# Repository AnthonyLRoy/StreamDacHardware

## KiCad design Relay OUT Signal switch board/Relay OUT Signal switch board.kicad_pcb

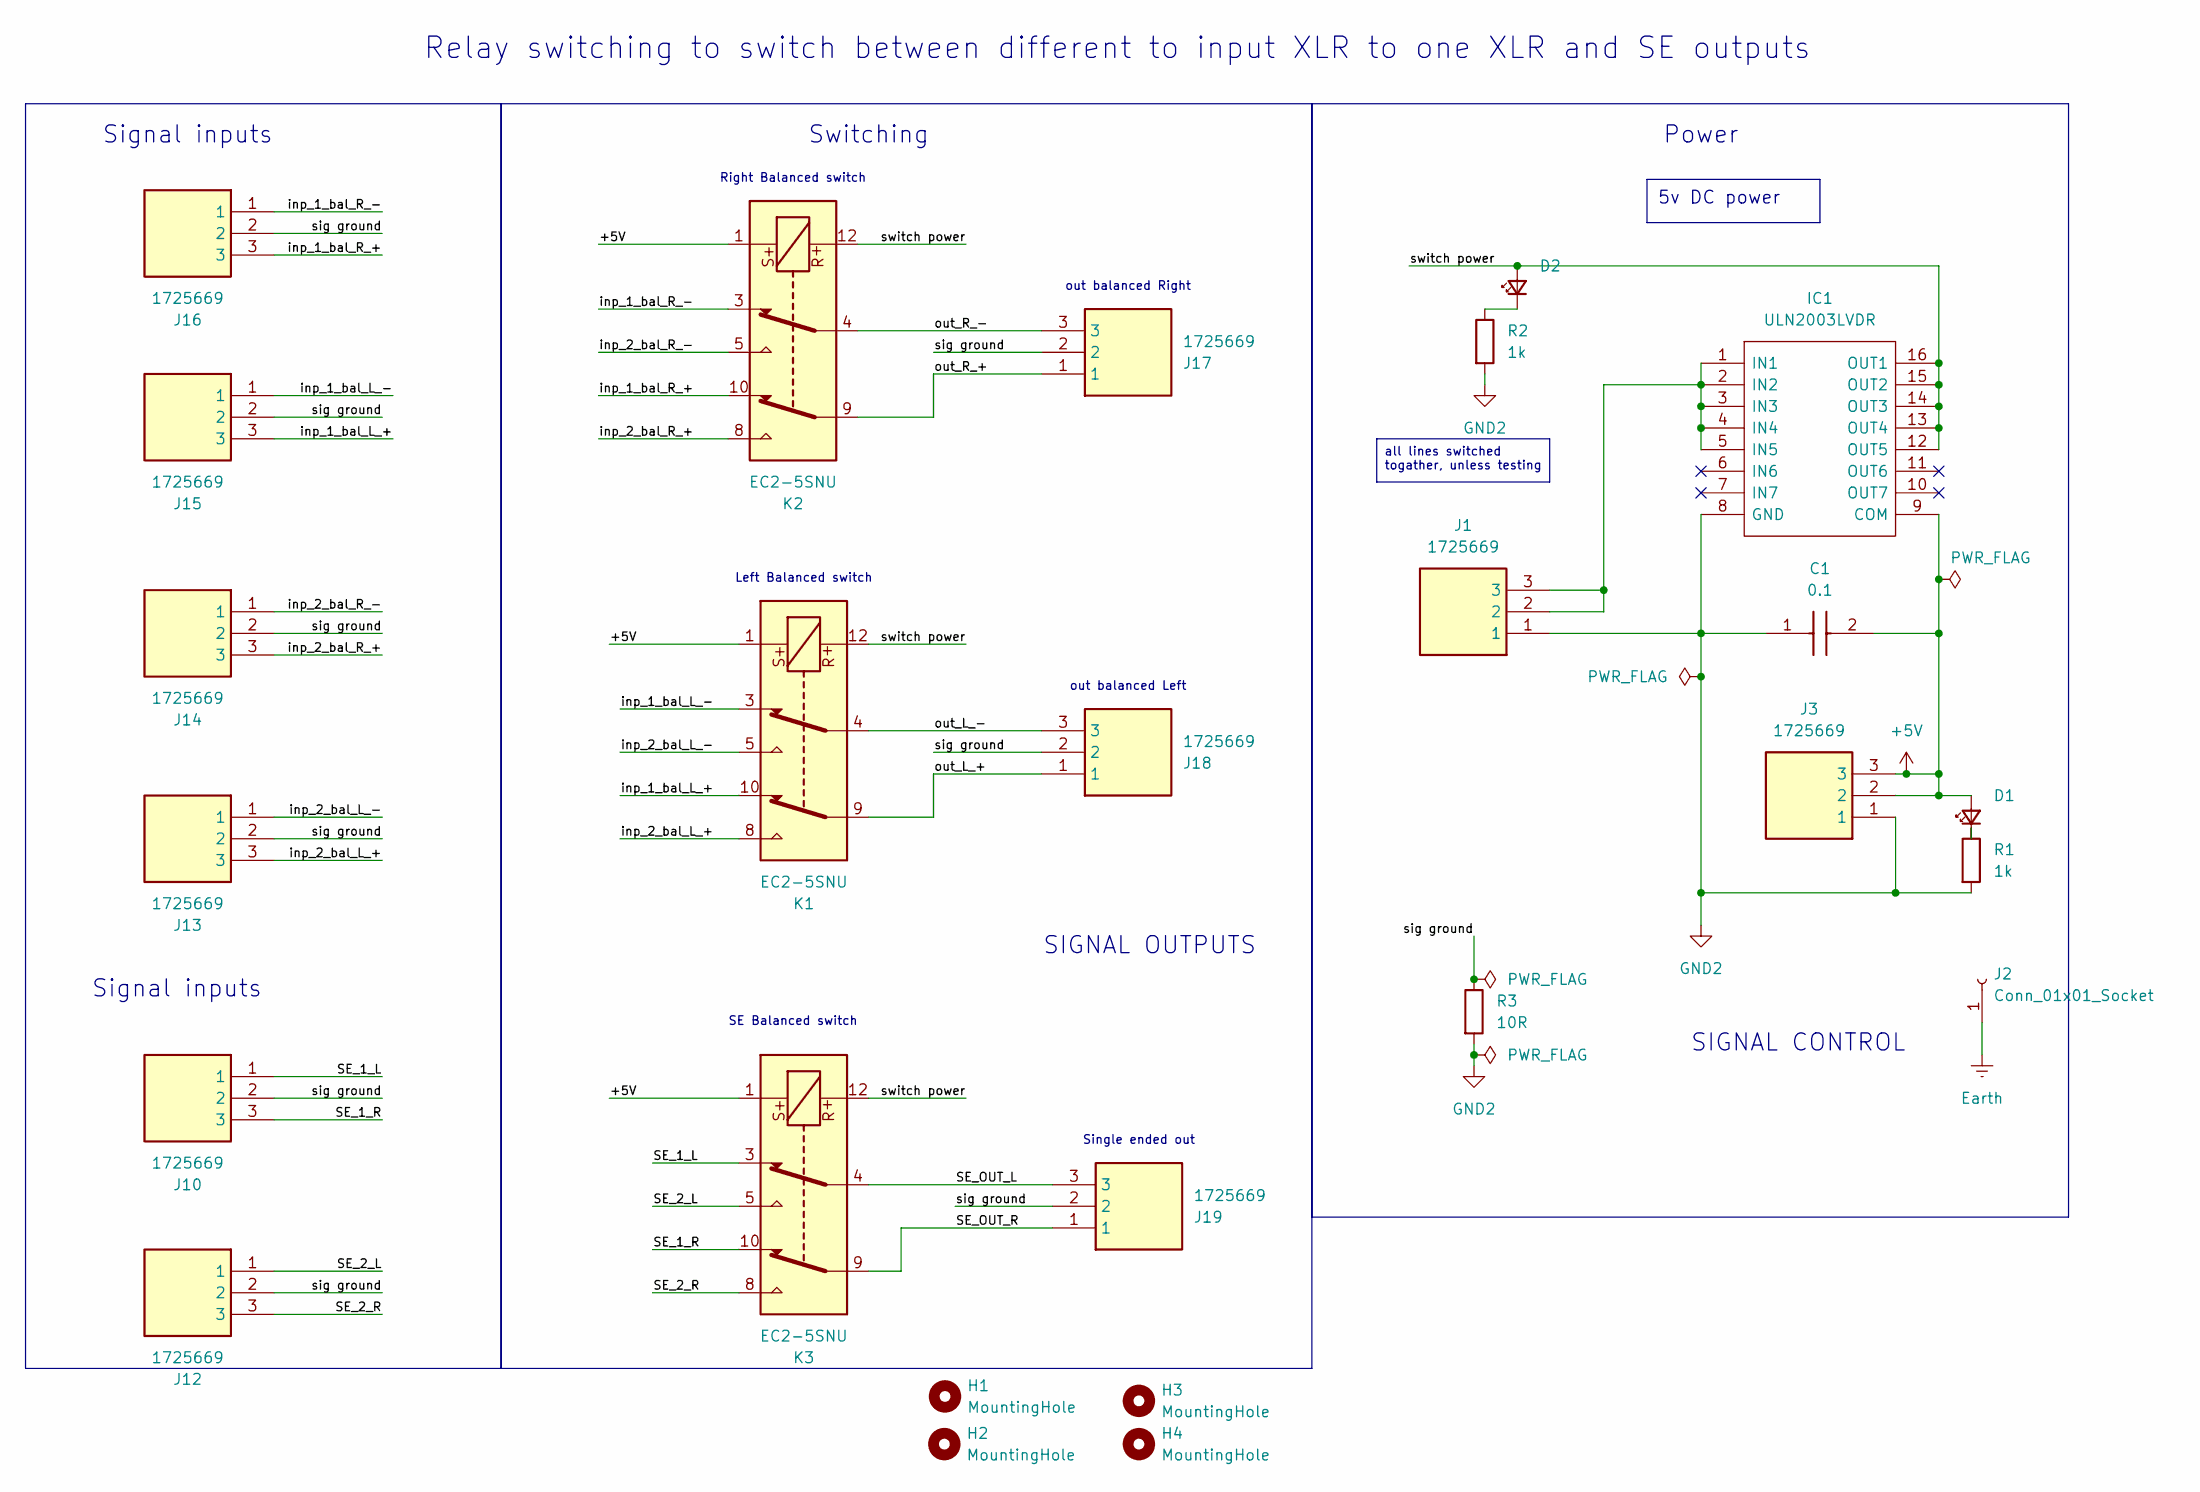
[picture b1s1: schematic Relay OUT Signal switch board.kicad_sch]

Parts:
C1: 0.1; C_0603_1608Metric; Mouser Part Number 80-C0603C104K4R3190
D1, D2: LS_R976; LEDC2012X40N; Mouser Part Number 720-LSR976D5178
H1, H2, H3, H4: MountingHole; MountingHole_2.5mm
IC1: ULN2003LVDR; SOIC127P780X200-16N; Manufacturer_Part_Number ULN2003LVDR; Mouser Part Number 595-ULN2003LVDR
J1, J3, J10, J12, J13, J14, J15, J16, J17, J18, J19: 1725669; Mouser Part Number 651-1725669
J2: Conn_01x01_Socket; PinHeader_1x01_P1.00mm_Vertical
K1, K2, K3: EC2-5SNU; Relay_DPDT_Kemet_EC2
R1, R2: 1k; R_0603_1608Metric
R3: 10R; R_0603_1608Metric

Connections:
+5V: C1.2, D1.2 (A), IC1.9 (COM), J3.2, J3.3, K1.1, K2.1, K3.1
/SE_1_L: J10.1, K3.3
/SE_1_R: J10.3, K3.10
/SE_2_L: J12.1, K3.5
/SE_2_R: J12.3, K3.8
/SE_OUT_L: J19.3, K3.4
/SE_OUT_R: J19.1, K3.9
/inp_1_bal_L_+: J15.3, K1.10
/inp_1_bal_L_-: J15.1, K1.3
/inp_1_bal_R_+: J16.3, K2.10
/inp_1_bal_R_-: J16.1, K2.3
/inp_2_bal_L_+: J13.3, K1.8
/inp_2_bal_L_-: J13.1, K1.5
/inp_2_bal_R_+: J14.3, K2.8
/inp_2_bal_R_-: J14.1, K2.5
/out_L_+: J18.1, K1.9
/out_L_-: J18.3, K1.4
/out_R_+: J17.1, K2.9
/out_R_-: J17.3, K2.4
/sig ground: J10.2, J12.2, J13.2, J14.2, J15.2, J16.2, J17.2, J18.2, J19.2, R3.1
/switch power: D2.2 (A), IC1.12 (OUT5), IC1.13 (OUT4), IC1.14 (OUT3), IC1.15 (OUT2), IC1.16 (OUT1), K1.12, K2.12, K3.12
Earth: J2.1
GND2: C1.1, IC1.8 (GND), J1.1, J3.1, R1.2, R2.2, R3.2
unnamed: D1.1 (K), R1.1
unnamed: D2.1 (K), R2.1
unnamed: IC1.1 (IN1), IC1.2 (IN2), IC1.3 (IN3), IC1.4 (IN4), IC1.5 (IN5), J1.2, J1.3

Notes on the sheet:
all lines switched togather, unless testing
5v DC power
out balanced Left
Left Balanced switch
Switching
Power
out balanced Right
Single ended out
Signal inputs
SIGNAL CONTROL
SE Balanced switch
Relay switching to switch between different to input XLR to one XLR and SE outputs
Right Balanced switch
SIGNAL OUTPUTS

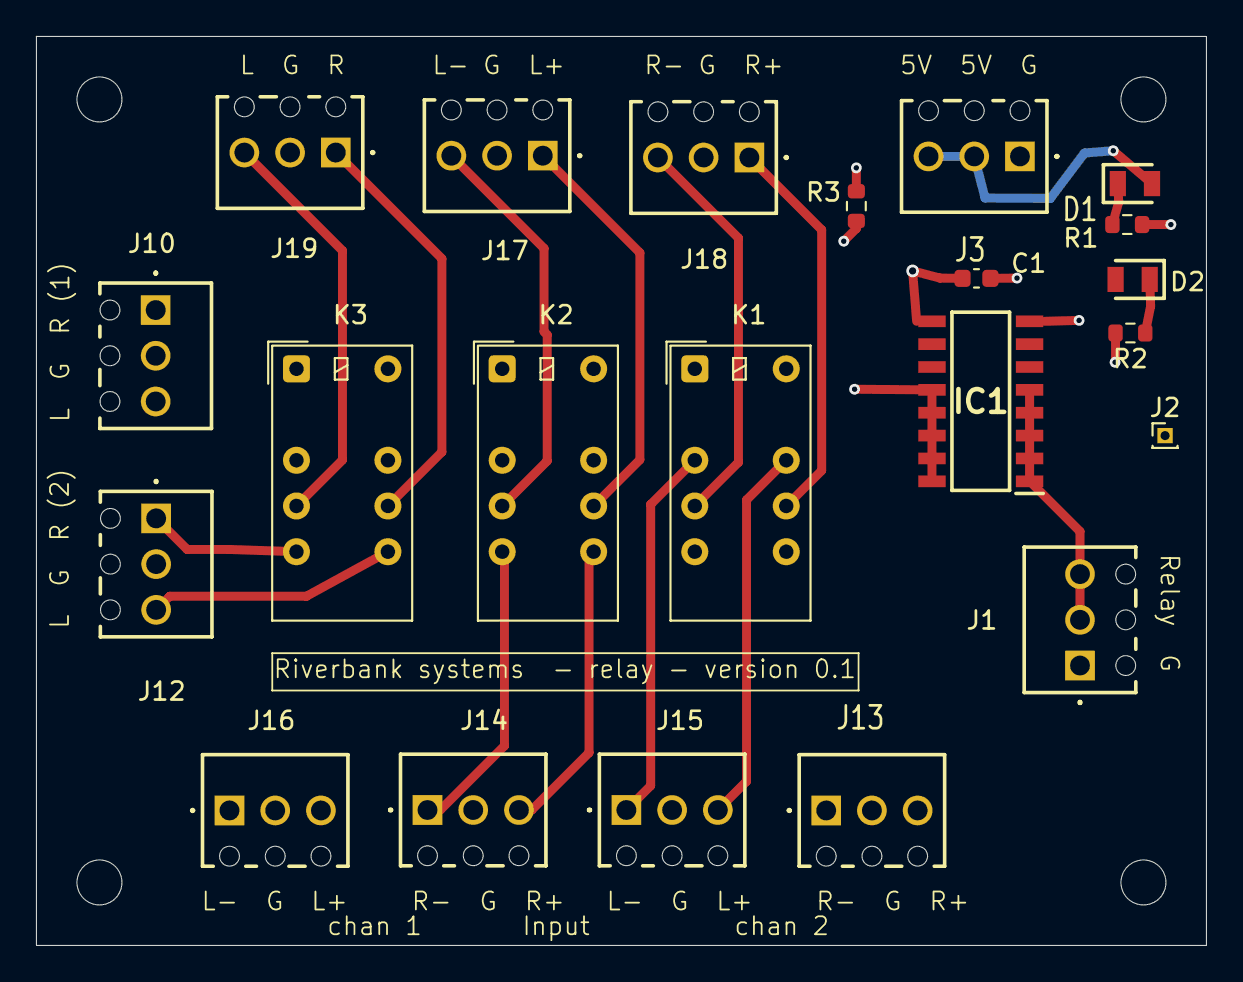
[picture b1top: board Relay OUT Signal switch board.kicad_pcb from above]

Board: 6 copper layers, 65.0 x 50.5 mm, 26 parts (0 on the bottom side), 25 nets.

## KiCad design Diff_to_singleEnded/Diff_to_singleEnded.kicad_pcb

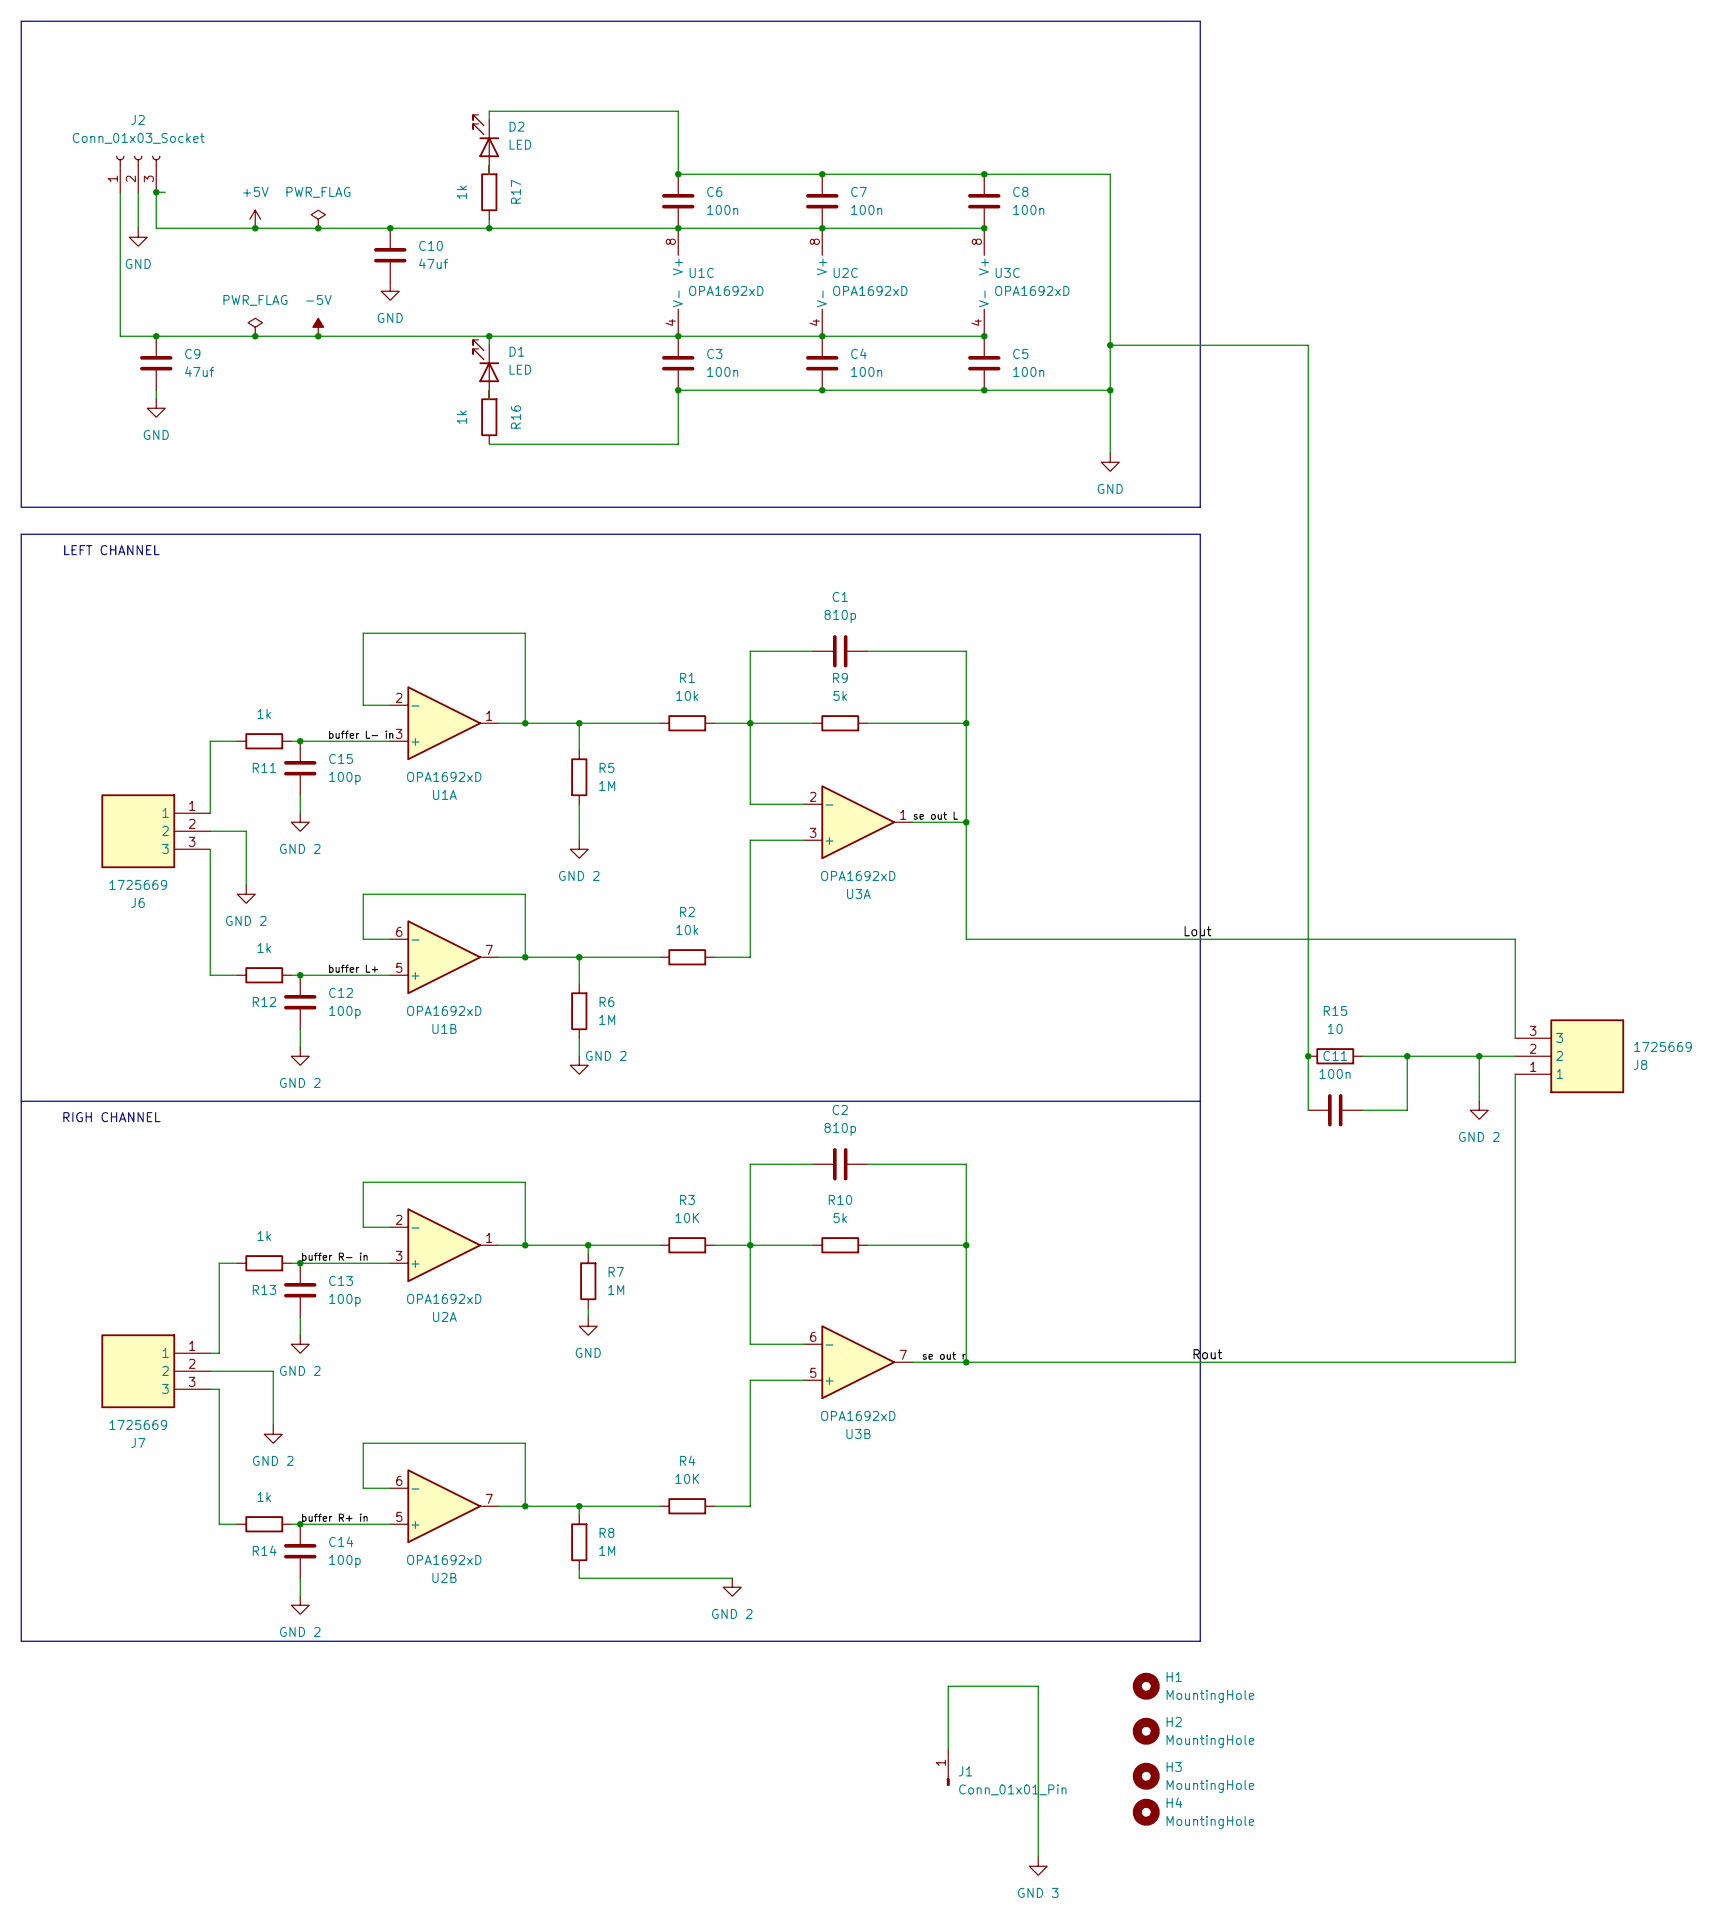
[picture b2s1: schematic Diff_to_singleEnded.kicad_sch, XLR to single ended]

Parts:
C1, C2: 810p; C_1206_3216Metric
C3, C4, C5, C6, C7, C8, C11: 100n; C_0805_2012Metric_Pad1.18x1.45mm_HandSolder
C9, C10: 47uf; CAPC3225X280N
C12, C13, C14, C15: 100p; C_0805_2012Metric
D1, D2: LED; LEDC2012X40N
H1, H2, H3, H4: MountingHole; MountingHole_2.7mm_M2.5
J1: Conn_01x01_Pin; PinHeader_1x01_P1.00mm_Vertical
J2: Conn_01x03_Socket; PhoenixContact_MCV_1,5_3-G-3.81_1x03_P3.81mm_Vertical
J6, J7, J8: 1725669; Mouser Part Number 651-1725669
R1, R2: 10k; R_Axial_DIN0309_L9.0mm_D3.2mm_P12.70mm_Horizontal
R3, R4: 10K; R_Axial_DIN0309_L9.0mm_D3.2mm_P12.70mm_Horizontal
R5, R6, R7, R8: 1M; R_Axial_DIN0309_L9.0mm_D3.2mm_P12.70mm_Horizontal
R9, R10: 5k; R_Axial_DIN0309_L9.0mm_D3.2mm_P12.70mm_Horizontal
R11, R12, R13, R14, R16, R17: 1k; R_0805_2012Metric
R15: 10; R_0603_1608Metric
U1, U2, U3: OPA1692xD; SOIC-8_3.9x4.9mm_P1.27mm

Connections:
+5V: C6.2, C7.2, C8.2, C10.1, J2.3, R17.1, U1.8 (V+), U2.8 (V+), U3.8 (V+)
-5V: C3.1, C4.1, C5.1, C9.1, D1.1 (K), J2.1, U1.4 (V-), U2.4 (V-), U3.4 (V-)
/Lout: C1.2, J8.3, R9.2, U3.1
/Rout: C2.2, J8.1, R10.2, U3.7
/buffer L+: C12.2, R12.2, U1.5 (+)
/buffer L- in: C15.2, R11.2, U1.3 (+)
/buffer R+ in: C14.2, R14.2, U2.5 (+)
/buffer R- in: C13.2, R13.2, U2.3 (+)
GND: C3.2, C4.2, C5.2, C6.1, C7.1, C8.1, C9.2, C10.2, C11.1, D2.1 (K), J2.2, R7.1, R15.1, R16.1
GND 2: C11.2, C12.1, C13.1, C14.1, C15.1, J6.2, J7.2, J8.2, R5.2, R6.1, R8.1, R15.2
GND 3: J1.1
unnamed: D1.2 (A), R16.2
unnamed: D2.2 (A), R17.2
unnamed: J6.1, R11.1
unnamed: J6.3, R12.1
unnamed: J7.1, R13.1
unnamed: J7.3, R14.1
unnamed: R1.1, R5.1, U1.1, U1.2 (-)
unnamed: R2.1, R6.2, U1.6 (-), U1.7
unnamed: R3.1, R7.2, U2.1, U2.2 (-)
unnamed: R4.1, R8.2, U2.6 (-), U2.7
unnamed: R2.2, U3.3 (+)
unnamed: C1.1, R1.2, R9.1, U3.2 (-)
unnamed: R4.2, U3.5 (+)
unnamed: C2.1, R3.2, R10.1, U3.6 (-)

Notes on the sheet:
LEFT CHANNEL
RIGH CHANNEL

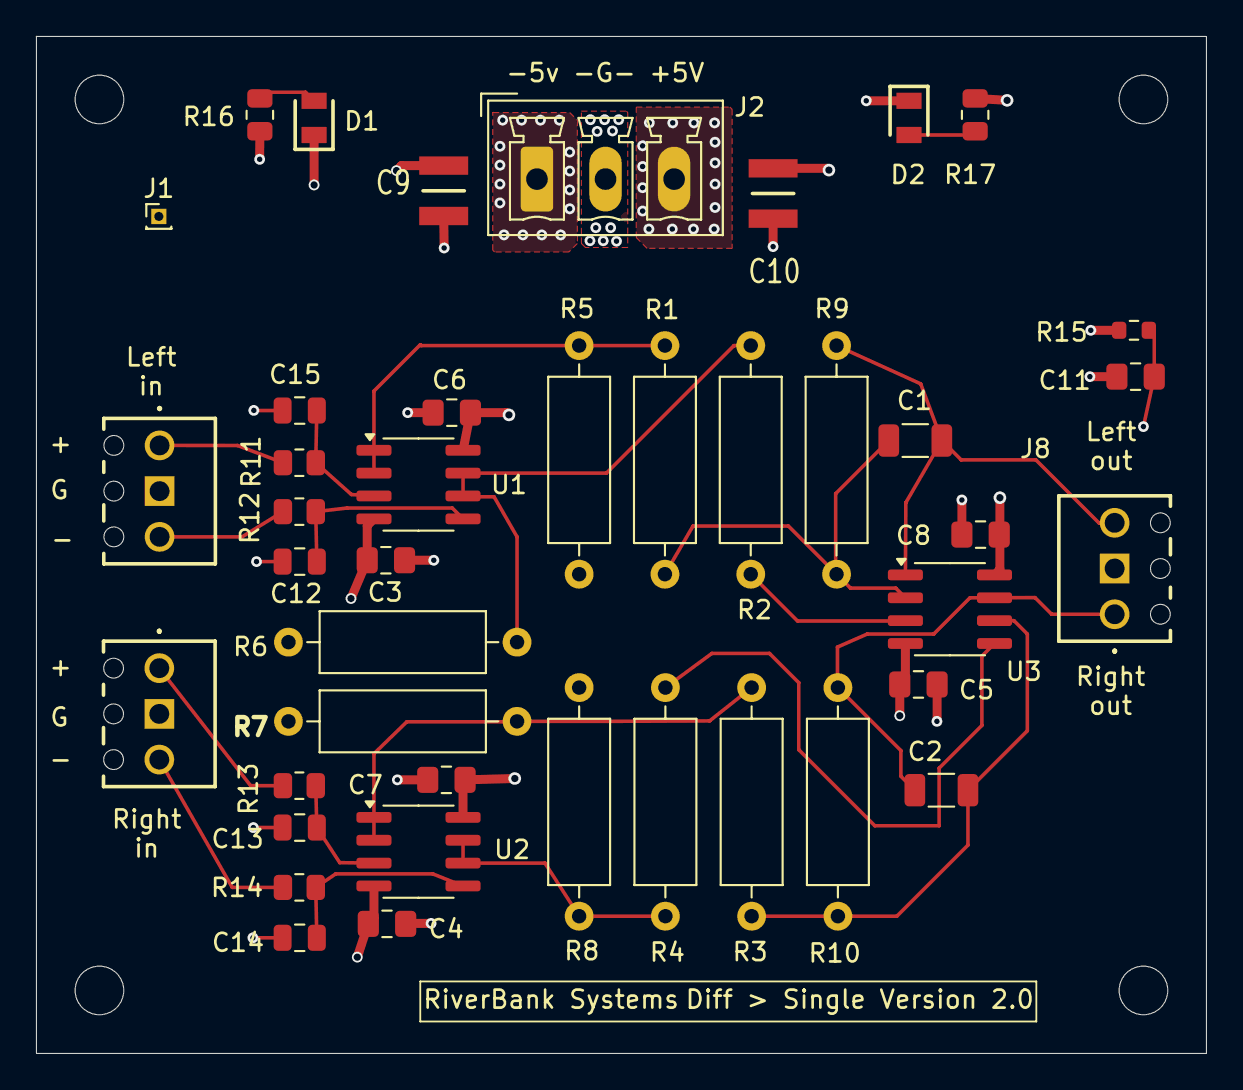
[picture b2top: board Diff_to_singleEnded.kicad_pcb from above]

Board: 6 copper layers, 65.0 x 56.5 mm, 46 parts (0 on the bottom side), 24 nets.

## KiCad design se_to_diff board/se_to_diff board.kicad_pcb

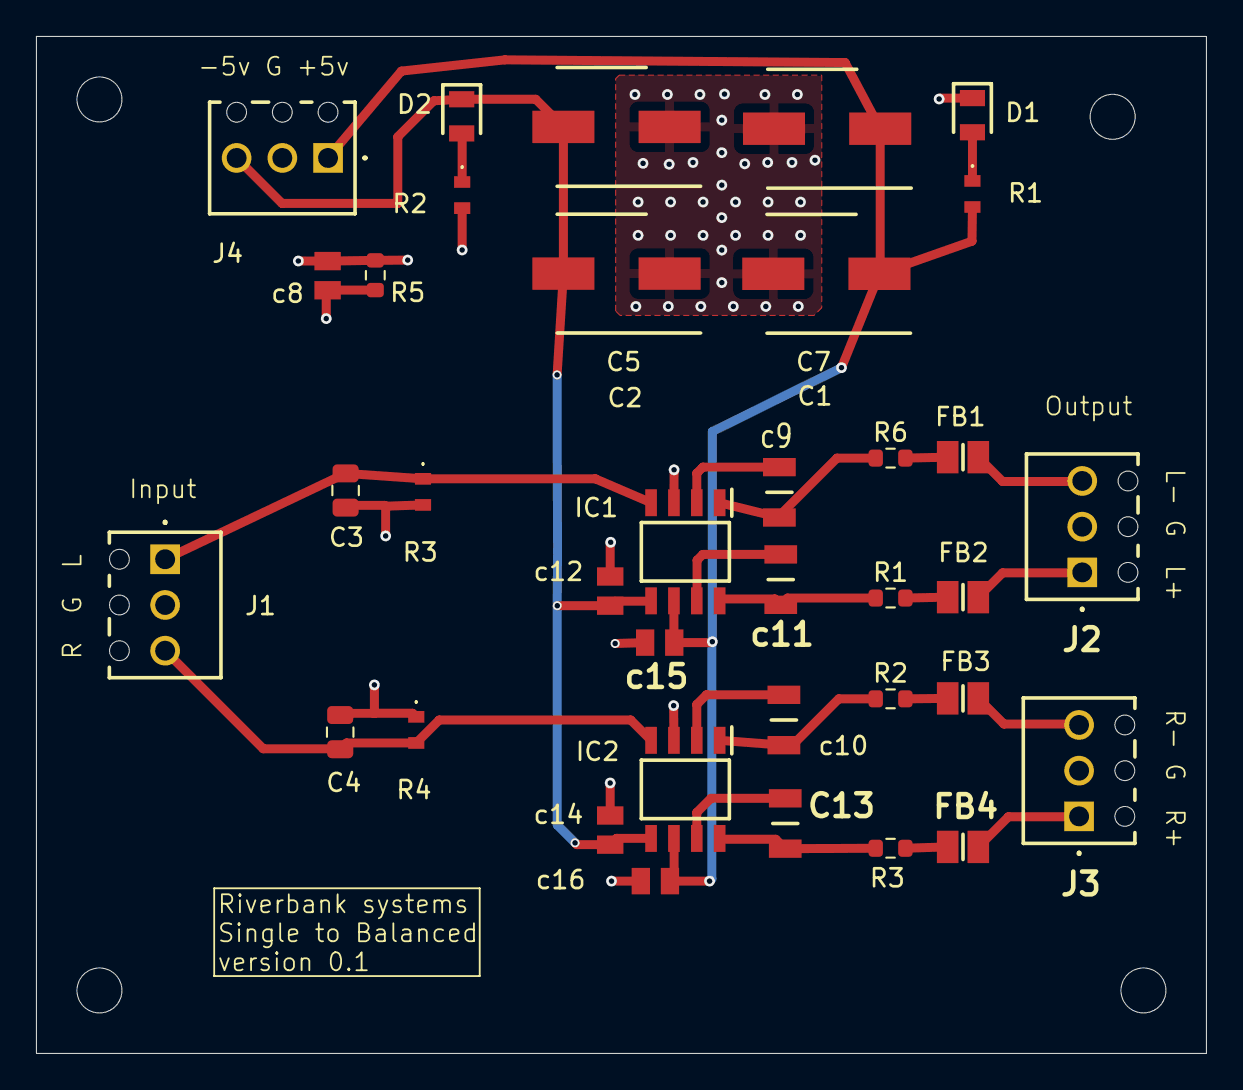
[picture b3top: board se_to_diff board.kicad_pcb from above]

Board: 4 copper layers, 65.0 x 56.5 mm, 40 parts (0 on the bottom side), 24 nets.

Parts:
C1, C2, C5, C7: 47u; CAPAE660X800N
C3, C4: 220p; C_0805_2012Metric
C13: 10u; CAPC3216X229N
D1, D2: LS_R976; LEDC2012X40N
FB1, FB2, FB3, FB4: NFZ2MSD101SZ10L; BEADC2016X120N
H1, H2, H3, H4: MountingHole; MountingHole_2.5mm
IC1, IC2: 1646S08-U; SOIC127P602X173-8N
J1, J2, J3, J4: 1725669
R1, R2#2, R3: 22; R_0603_1608Metric
R1#2, R2: 3k; ERJH3
R3#2, R4: 47k; ERJH3
R5: 10R; R_0603_1608Metric
R6: 22R; R_0603_1608Metric
c8, c12, c14, c15, c16: 100n; CAPC2012X94N
c9, c10, c11: 10u; CAPC3216X229N

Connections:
/Sout L +: FB2.1, R1.2
/Sout L -: FB1.1, R6.2
/Sout R +: FB4.1, R3.2
/Sout R -: FB3.1, R2#2.2
/in L: C3.2, IC1.4 (IN), J1.1, R3#2.1
/in R: C4.1, IC2.4 (IN), J1.3, R4.2
/out L +: IC1.8 (OUT+), R1.1, c11.2
/out L -: IC1.1 (OUT-), R6.1, c9.2
/out R +: C13.2, IC2.8 (OUT+), R3.1
/out R -: IC2.1 (OUT-), R2#2.1, c10.2
GND: C3.1, C4.2, IC1.3 (GND), IC2.3 (GND), J1.2, J2.2, J3.2, R3#2.2, R4.1, R5.2, c8.1
GND2: C1.2, C2.1, C5.1, C7.2, D1.1 (K), J4.2, R2.2, R5.1, c8.2, c12.1, c14.1, c15.1, c16.1
unnamed: D1.2 (A), R1#2.1
unnamed: D2.2 (A), R2.1
unnamed: FB1.2, J2.3
unnamed: FB2.2, J2.1
unnamed: FB3.2, J3.3
unnamed: FB4.2, J3.1
unnamed: IC1.7 (SNS+), c11.1
unnamed: IC1.2 (SNS-), c9.1
unnamed: C13.1, IC2.7 (SNS+)
unnamed: IC2.2 (SNS-), c10.1
VCC: C1.1, C7.1, IC1.6 (VCC), IC2.6 (VCC), J4.1, R1#2.2, c15.2, c16.2
VEE: C2.2, C5.2, D2.1 (K), IC1.5 (VEE), IC2.5 (VEE), J4.3, c12.2, c14.2

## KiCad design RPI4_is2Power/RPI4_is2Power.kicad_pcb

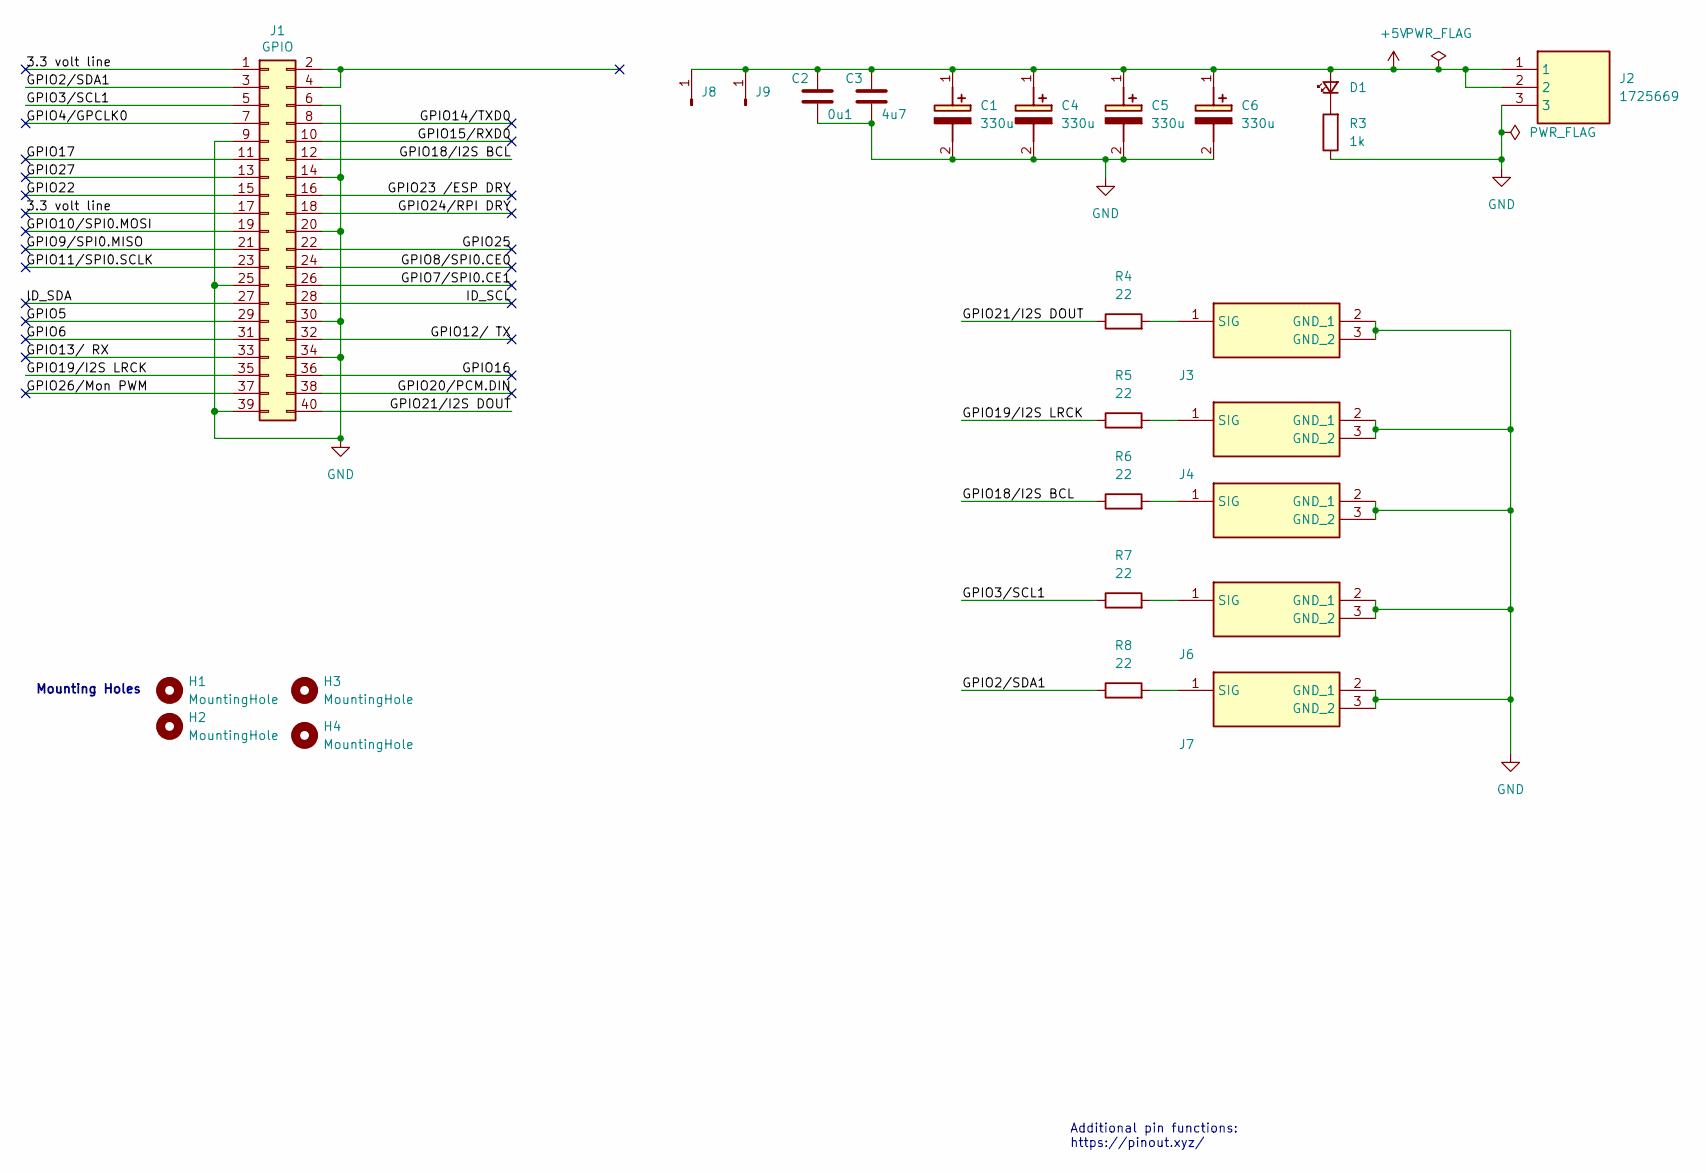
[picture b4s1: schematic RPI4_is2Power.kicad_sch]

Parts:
C1, C4, C5, C6: 330u; CAPPRD350W60D800H1300; Mouser Part Number 647-RNU1C331MDN1KX
C2: 0u1; C_0603_1608Metric_Pad1.08x0.95mm_HandSolder
C3: 4u7; CP_Radial_D5.0mm_P2.00mm
D1: LS_R976; LEDC2012X40N; Mouser Part Number 720-LSR976D5178
H1, H2, H3, H4: MountingHole; MountingHole_2.5mm
J1: GPIO; PinSocket_2x20_P2.54mm_Vertical
J2: 1725669; Mouser Part Number 651-1725669
J3, J4, J5, J6, J7: U.FL-R-SMT-1_80_; UFLRSMT180; Manufacturer_Part_Number U.FL-R-SMT-1(80)
J8, J9: Conn_01x01_Pin; Pin_D1.2mm_L11.3mm_W3.0mm_Flat
R3: 1k; R_0402_1005Metric
R4, R5, R6, R7, R8: 22; R_0402_1005Metric

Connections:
+5V: C1.1 (+), C2.1, C3.1, C4.1 (+), C5.1 (+), C6.1 (+), D1.2 (A), J2.1, J2.2, J8.1, J9.1
/3.3 volt line: J1.1, J1.17
/GPIO2/SDA1: J1.3, R8.1
/GPIO3/SCL1: J1.5, R7.1
/GPIO4/GPCLK0: J1.7
/GPIO5: J1.29
/GPIO6: J1.31
/GPIO7/SPI0.CE1: J1.26
/GPIO8/SPI0.CE0: J1.24
/GPIO9/SPI0.MISO: J1.21
/GPIO10/SPI0.MOSI: J1.19
/GPIO11/SPI0.SCLK: J1.23
/GPIO12/ TX: J1.32
/GPIO13/ RX: J1.33
/GPIO14/TXD0: J1.8
/GPIO15/RXD0: J1.10
/GPIO16: J1.36
/GPIO17: J1.11
/GPIO18/I2S BCL: J1.12, R6.1
/GPIO19/I2S LRCK: J1.35, R5.1
/GPIO20/PCM.DIN: J1.38
/GPIO21/I2S DOUT: J1.40, R4.1
/GPIO22: J1.15
/GPIO23 /ESP DRY: J1.16
/GPIO24/RPI DRY: J1.18
/GPIO25: J1.22
/GPIO26/Mon PWM: J1.37
/GPIO27: J1.13
/ID_SCL: J1.28
/ID_SDA: J1.27
GND: C1.2 (-), C2.2, C3.2, C4.2 (-), C5.2 (-), C6.2 (-), J1.6, J1.9, J1.14, J1.20, J1.25, J1.30, J1.34, J1.39, J2.3, J3.2 (GND_1), J3.3 (GND_2), J4.2 (GND_1), J4.3 (GND_2), J5.2 (GND_1), J5.3 (GND_2), J6.2 (GND_1), J6.3 (GND_2), J7.2 (GND_1), J7.3 (GND_2), R3.1
unnamed: D1.1 (K), R3.2
unnamed: J3.1 (SIG), R4.2
unnamed: J4.1 (SIG), R5.2
unnamed: J5.1 (SIG), R6.2
unnamed: J6.1 (SIG), R7.2
unnamed: J7.1 (SIG), R8.2

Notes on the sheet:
Mounting Holes
Additional pin functions: https://pinout.xyz/

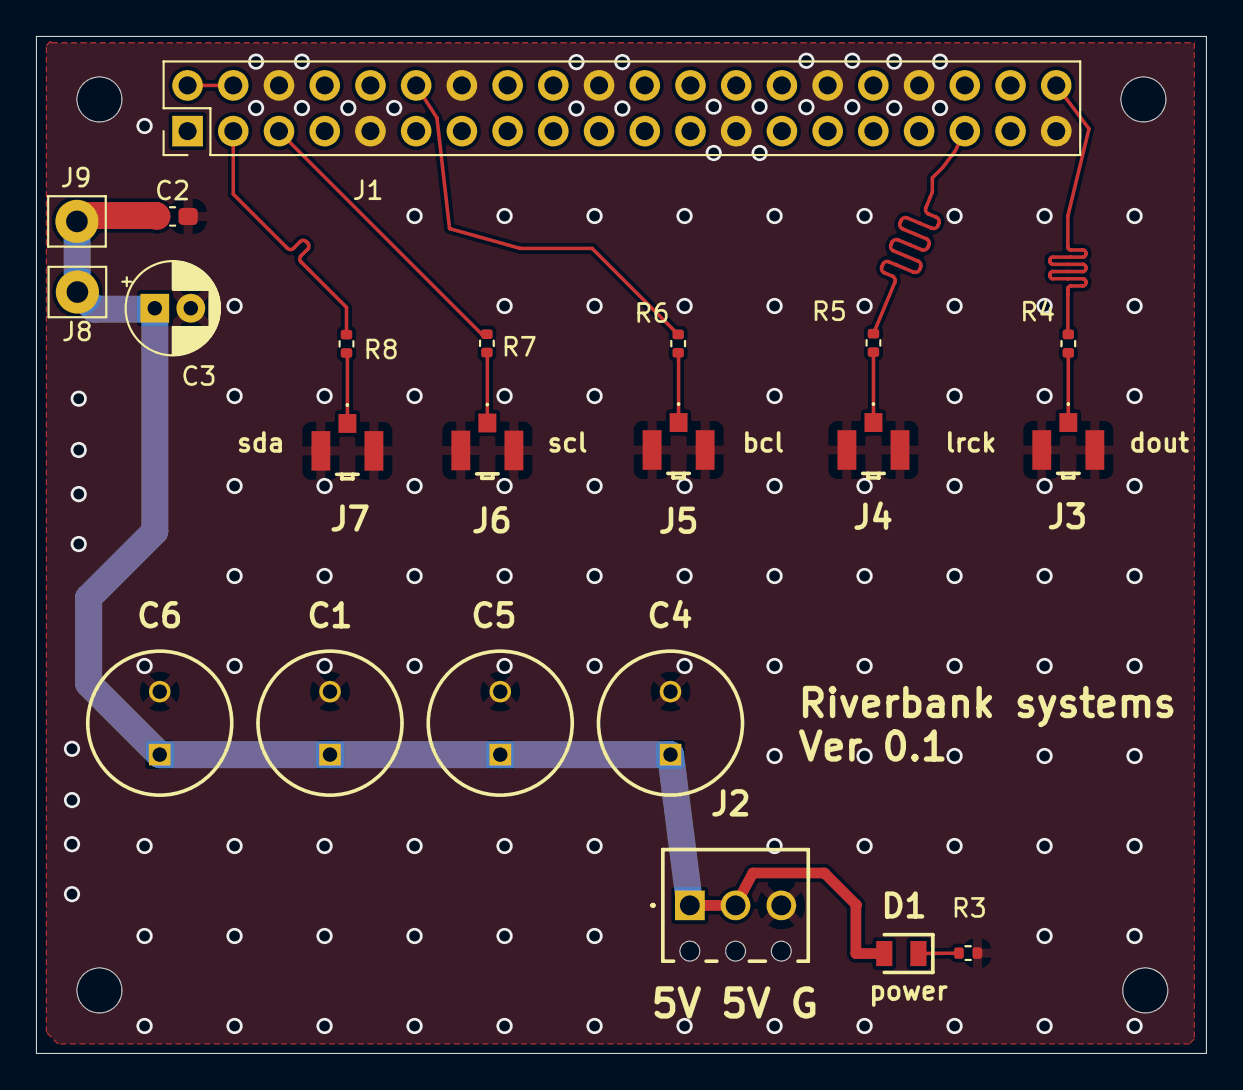
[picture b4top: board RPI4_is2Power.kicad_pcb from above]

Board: 2 copper layers, 65.0 x 56.5 mm, 26 parts (0 on the bottom side), 14 nets.

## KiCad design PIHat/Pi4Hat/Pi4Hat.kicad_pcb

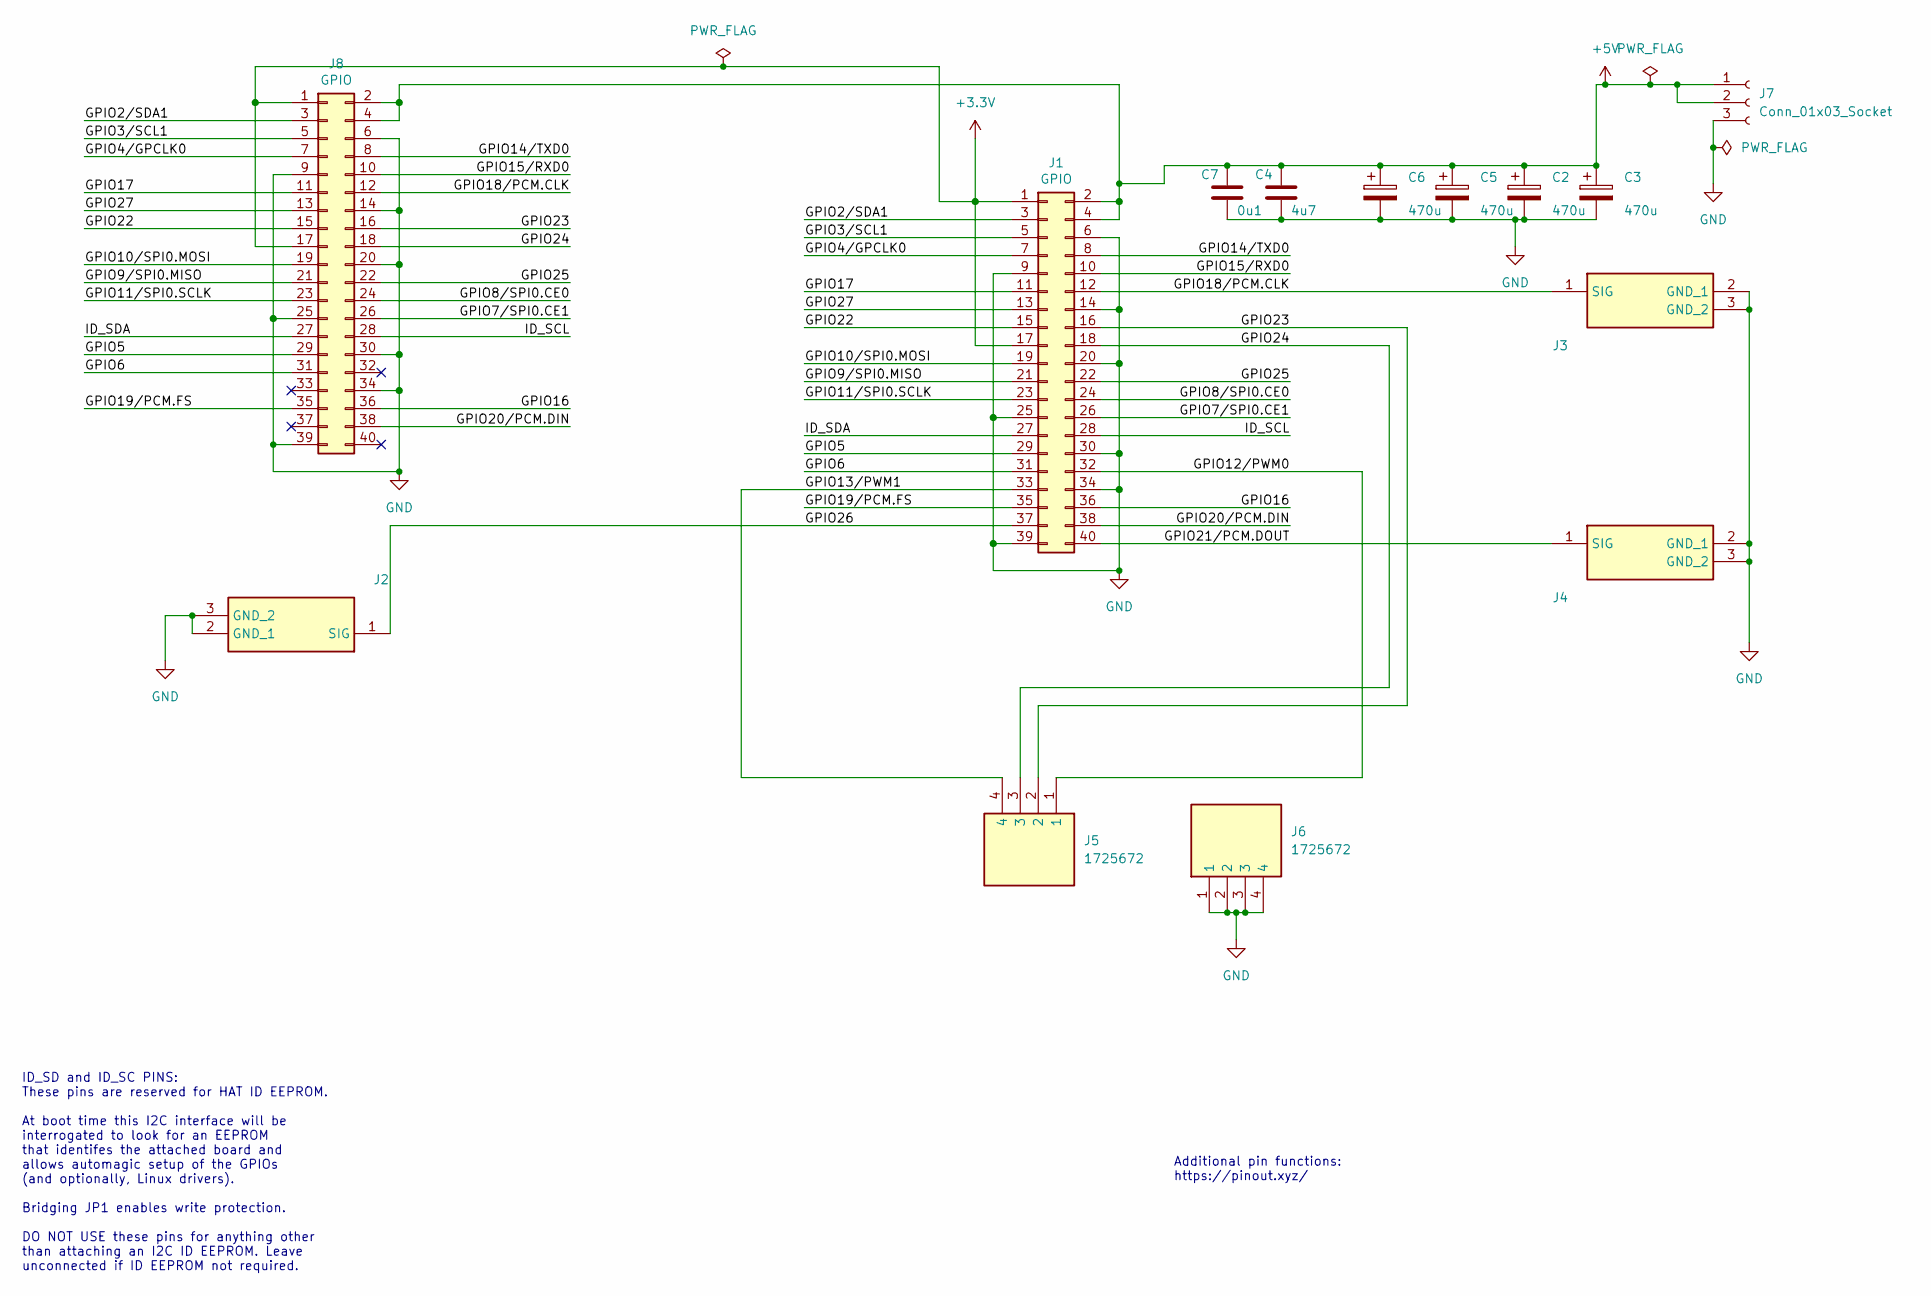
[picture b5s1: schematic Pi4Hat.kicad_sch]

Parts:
C2, C3, C5, C6: 470u; CP_Radial_D13.0mm_P5.00mm
C4: 4u7; CP_Radial_D5.0mm_P2.00mm
C7: 0u1; C_0603_1608Metric_Pad1.08x0.95mm_HandSolder
J1, J8: GPIO; PinSocket_2x20_P2.54mm_Vertical
J2, J3, J4: U.FL-R-SMT-1_80_; UFLRSMT180; Manufacturer_Part_Number U.FL-R-SMT-1(80)
J5, J6: 1725672; Mouser Part Number 651-1725672
J7: Conn_01x03_Socket; PCB Wired Socket

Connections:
+3.3V: J1.1, J1.17, J8.1, J8.17
+5V: C2.1, C3.1, C4.1, C5.1, C6.1, C7.1, J1.2, J1.4, J7.1, J7.2, J8.2, J8.4
/GPIO2/SDA1: J1.3, J8.3
/GPIO3/SCL1: J1.5, J8.5
/GPIO4/GPCLK0: J1.7, J8.7
/GPIO5: J1.29, J8.29
/GPIO6: J1.31, J8.31
/GPIO7/SPI0.CE1: J1.26, J8.26
/GPIO8/SPI0.CE0: J1.24, J8.24
/GPIO9/SPI0.MISO: J1.21, J8.21
/GPIO10/SPI0.MOSI: J1.19, J8.19
/GPIO11/SPI0.SCLK: J1.23, J8.23
/GPIO12/PWM0: J1.32, J5.1
/GPIO13/PWM1: J1.33, J5.4
/GPIO14/TXD0: J1.8, J8.8
/GPIO15/RXD0: J1.10, J8.10
/GPIO16: J1.36, J8.36
/GPIO17: J1.11, J8.11
/GPIO18/PCM.CLK: J1.12, J3.1 (SIG), J8.12
/GPIO19/PCM.FS: J1.35, J8.35
/GPIO20/PCM.DIN: J1.38, J8.38
/GPIO21/PCM.DOUT: J1.40, J4.1 (SIG)
/GPIO22: J1.15, J8.15
/GPIO23: J1.16, J5.2, J8.16
/GPIO24: J1.18, J5.3, J8.18
/GPIO25: J1.22, J8.22
/GPIO26: J1.37, J2.1 (SIG)
/GPIO27: J1.13, J8.13
/ID_SCL: J1.28, J8.28
/ID_SDA: J1.27, J8.27
GND: C2.2, C3.2, C4.2, C5.2, C6.2, C7.2, J1.6, J1.9, J1.14, J1.20, J1.25, J1.30, J1.34, J1.39, J2.2 (GND_1), J2.3 (GND_2), J3.2 (GND_1), J3.3 (GND_2), J4.2 (GND_1), J4.3 (GND_2), J6.1, J6.2, J6.3, J6.4, J7.3, J8.6, J8.9, J8.14, J8.20, J8.25, J8.30, J8.34, J8.39

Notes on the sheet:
Additional pin functions: https://pinout.xyz/
ID_SD and ID_SC PINS: These pins are reserved for HAT ID EEPROM. At boot time this I2C interface will be interrogated to look for an EEPROM that identifes the attached board and allows automagic setup of the GPIOs (and optionally, Linux drivers). Bridging JP1 enables write protection. DO NOT USE th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

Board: 2 copper layers, 18 parts (1 on the bottom side), 31 nets, no tracks yet.

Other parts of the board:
MH1, MH2, MH3, MH4: MountingHole_2.7mm_M2.5
